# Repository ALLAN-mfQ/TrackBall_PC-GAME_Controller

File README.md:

## update

2022/12/18  
ジャイロセンサーを追加しました。  

メインボードを新しくしてMPU6050を搭載しました。  
新しい基板はボタンを2つ追加できるようにしてあります。　必要に応じて改造可能です。  
[+GYRO](https://github.com/ALLAN-mfQ/TrackBall_PC-GAME_Controller/tree/main/%2BGYRO)にデータを公開しています。

・メインボードのシルクが一部間違っていたので修正しました。　×　BS.L　→　〇 RB.R  
・KiCadのプロジェクトファイルを公開しました。  

# TrackBall PC GAME Controller

キーボードとマウスとして認識します。  
3Dデータは6.08インチの光造形3Dプリンターで印刷可能です。  
  
This is recognized as a keyboard and mouse when viewed from a PC.  
3D data can be printed with a 6.08" resin 3D printer.  
  
## YouTube

# Add library to Arduino IDE.  
  
- https://github.com/zapmaker/OptiMouse  
OptiMouse replaces ADNS2083.cpp and ADNS2083.h with ["OptiMouse_MX8650_fix setting"](https://github.com/ALLAN-mfQ/TrackBall_PC-GAME_Controller/tree/main/Source%20code/OptiMouse_MX8650_fix%20setting).  
  
- https://github.com/nickgammon/Keypad_Matrix  

- https://github.com/PaulStoffregen/Encoder  

--------------------------------------------
#### Placement of programmed switches

-------------------------  
# Fusion360 Viewer

- ## [CAD DATA](https://github.com/ALLAN-mfQ/TrackBall_PC-GAME_Controller/releases/tag/f3z)  
  
-------------------------  
# Social
- [YouTube](https://www.youtube.com/channel/UCiIz3zCHwNroYE9h4h5BDew)  
- [blog](http://ftukurou.blog41.fc2.com/)  
- [Twitter](https://twitter.com/Qdegozaimasu)  
------------------------  
# License
<br />この 作品 は <a rel="license" href="http://creativecommons.org/licenses/by-nc-sa/4.0/">クリエイティブ・コモンズ 表示 - 非営利 - 継承 4.0 国際 ライセンス</a>の下に提供されています。  
  
You are free to:  
- Share — copy and redistribute the material in any medium or format  
- Adapt — remix, transform, and build upon the material  
The licensor cannot revoke these freedoms as long as you follow the license terms.  
  
Under the following terms:  
- Attribution — You must give appropriate credit, provide a link to the license, and indicate if changes were made. You may do so in any reasonable manner, but not in any way that suggests the licensor endorses you or your use.  
  
- NonCommercial — You may not use the material for commercial purposes.  
  
- ShareAlike — If you remix, transform, or build upon the material, you must distribute your contributions under the same license as the original.  
  
- No additional restrictions — You may not apply legal terms or technological measures that legally restrict others from doing anything the license permits.

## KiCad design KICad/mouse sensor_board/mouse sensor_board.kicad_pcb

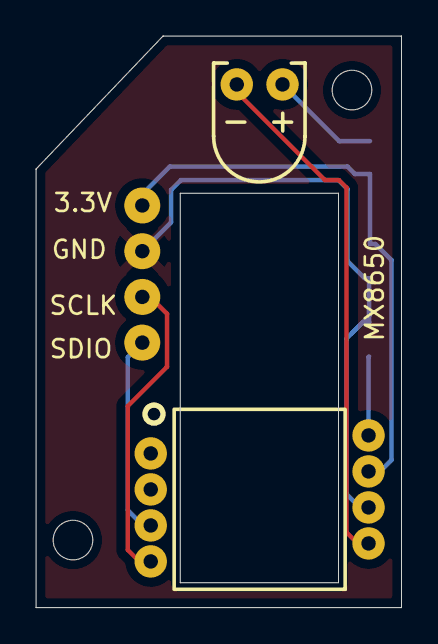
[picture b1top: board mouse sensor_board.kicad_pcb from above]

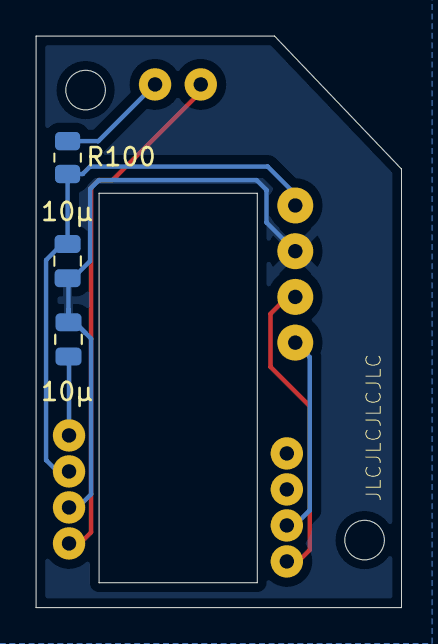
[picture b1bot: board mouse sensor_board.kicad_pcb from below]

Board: 2 copper layers, 20.3 x 31.8 mm, 6 parts (3 on the bottom side), 3 nets.

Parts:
3.3V: pad_1p
10μ: C10μ; C_0805_2012Metric
10μ#2: C; C_0805_2012Metric
GND: pad_1p
R100: R; R_0805_2012Metric
U1: MX8650; MX89650

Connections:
+3V3: 3.3V.1, 10μ.1, R100.2, U1.7 (VDD)
GND: 10μ.2, 10μ#2.2, GND.1, U1.6 (GND)
unnamed: 10μ#2.1, U1.8 (VDDA)

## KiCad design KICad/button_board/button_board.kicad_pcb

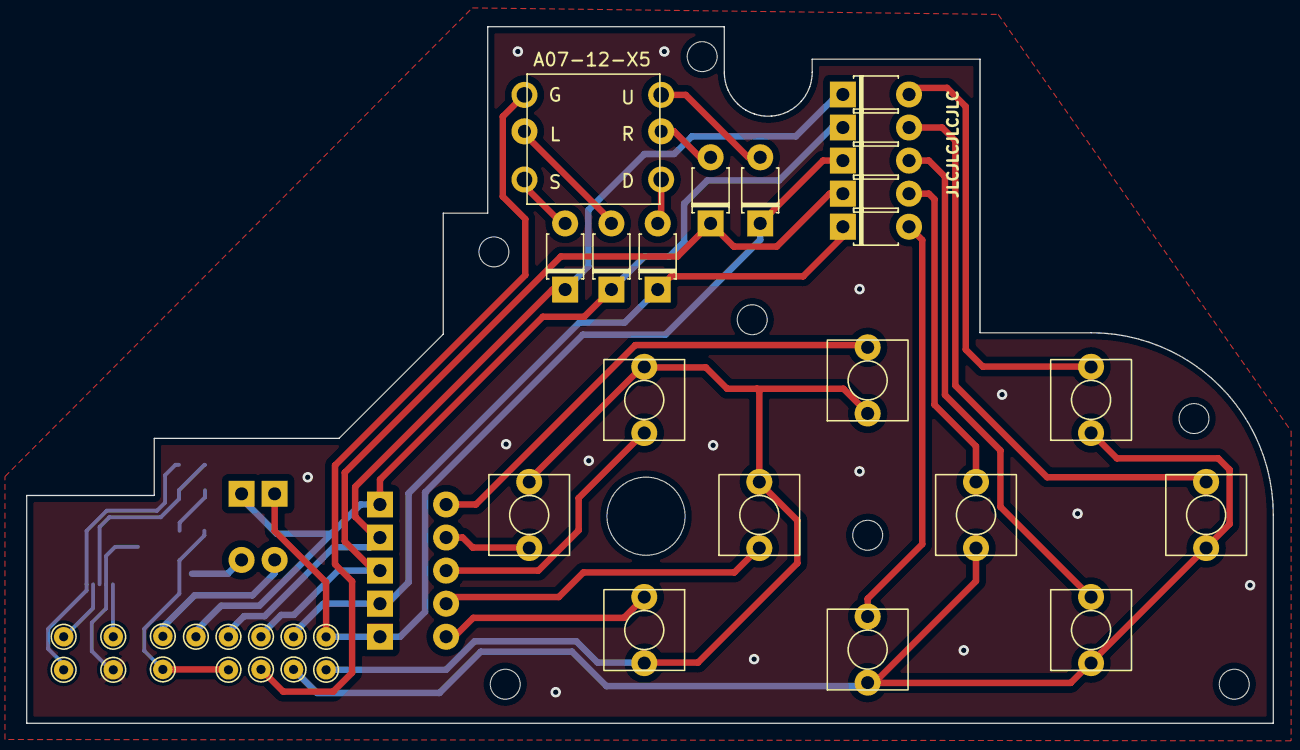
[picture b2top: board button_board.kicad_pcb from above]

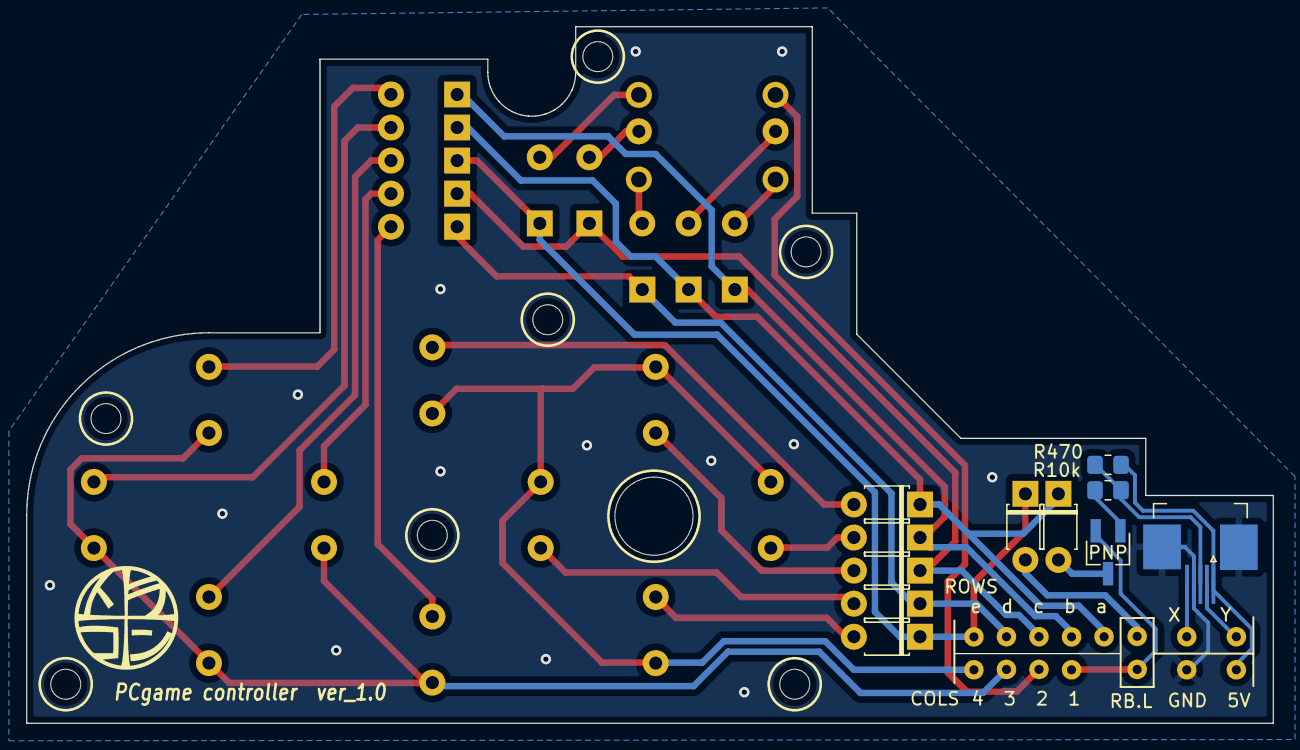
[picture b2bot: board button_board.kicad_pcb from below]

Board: 2 copper layers, 95.8 x 53.5 mm, 4 parts (3 on the bottom side), 2 nets.

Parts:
A07-12-X5: A07-12-X5
PNP: SC-59_Handsoldering
R10k, R470: R_0805_2012Metric_Pad1.20x1.40mm_HandSolder

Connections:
jsw: R10k.2, R470.1
jsw2: PNP.1, R10k.1

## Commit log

2022-09-13 Create library download link
2022-09-13 Rename library download link to library download link.txt
2022-09-13 Update and rename library download link.txt to library download link
2022-09-13 Create image

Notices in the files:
README.md:
License:
CC BY-NC-SA 4.0
